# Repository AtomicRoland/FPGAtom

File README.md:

# FPGAtom

These are the KiCad files of the MK2 boards for the Atom 2k18 a.k.a. FPGAtom. The production files of the MK1 boards are also included but you don't want to use these :-).

For support, create an issue on Github or post your question or remark on the StarDot forums: https://stardot.org.uk/forums/viewtopic.php?f=44&t=15197

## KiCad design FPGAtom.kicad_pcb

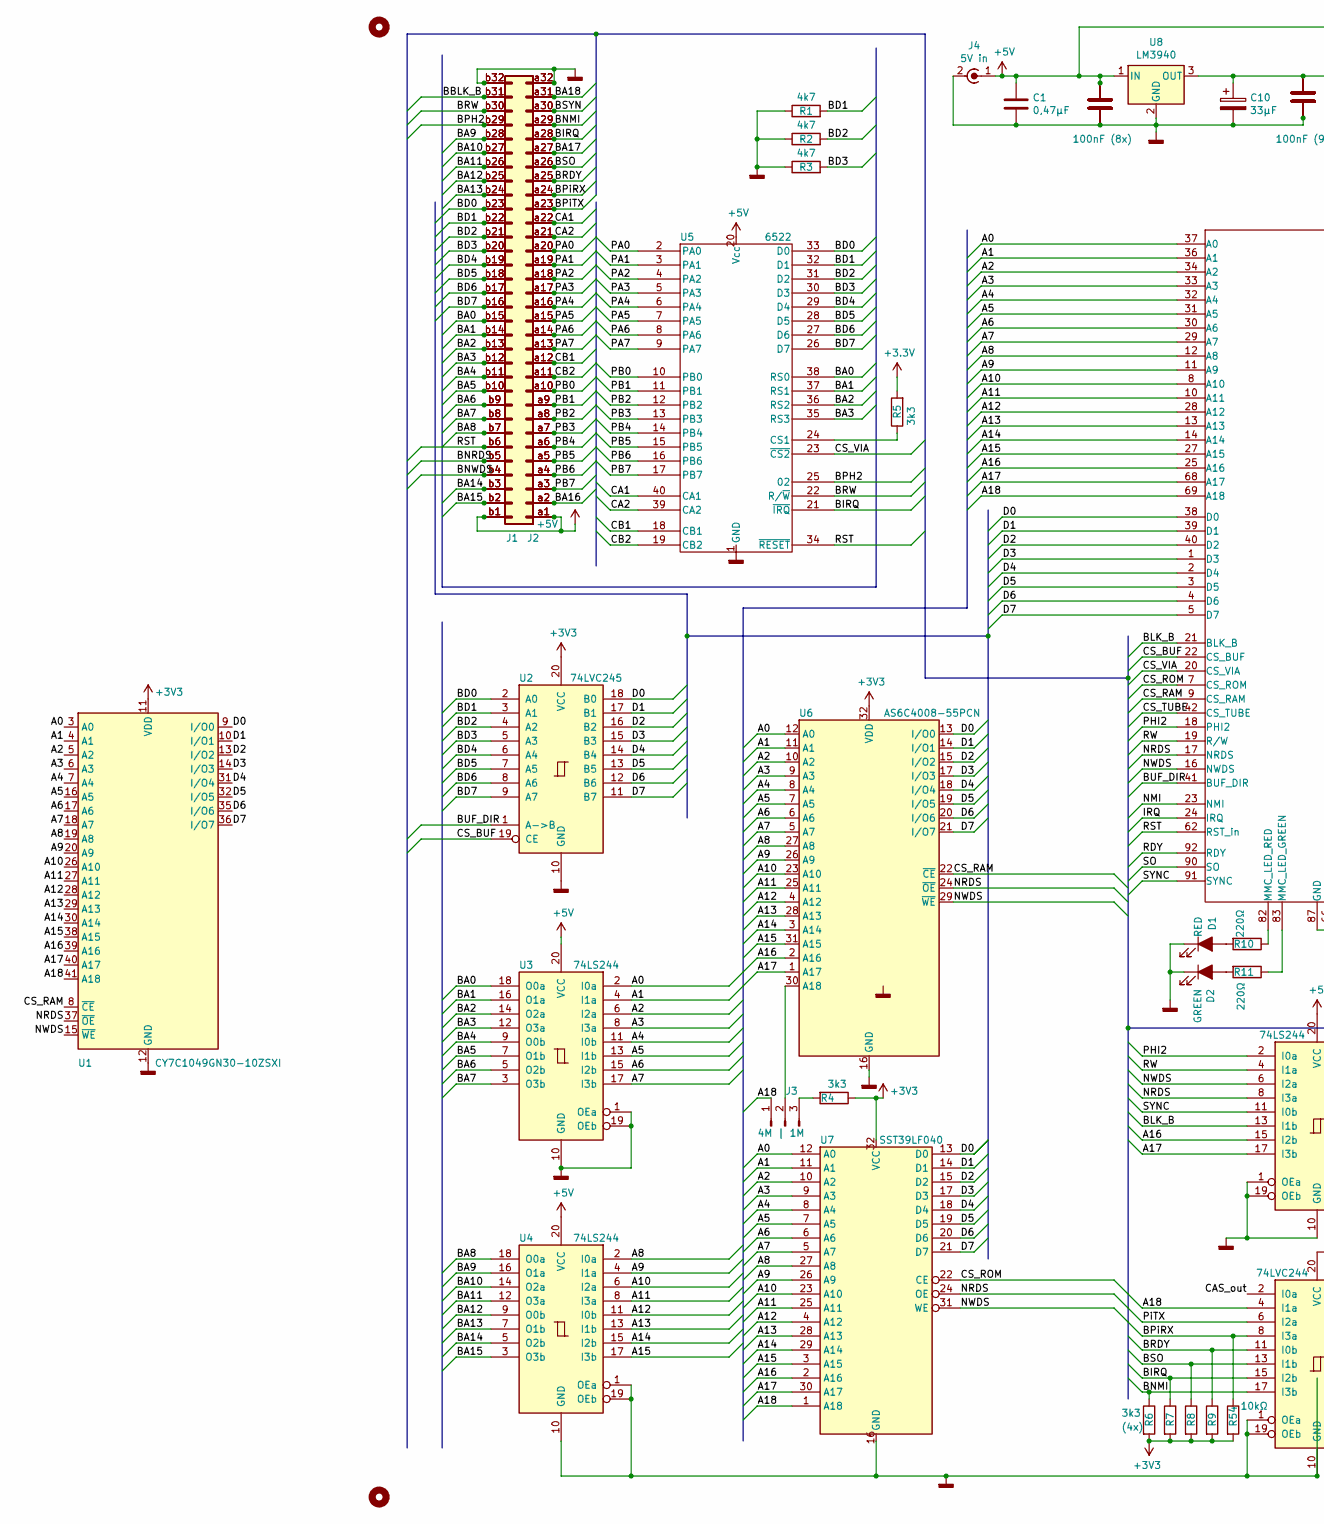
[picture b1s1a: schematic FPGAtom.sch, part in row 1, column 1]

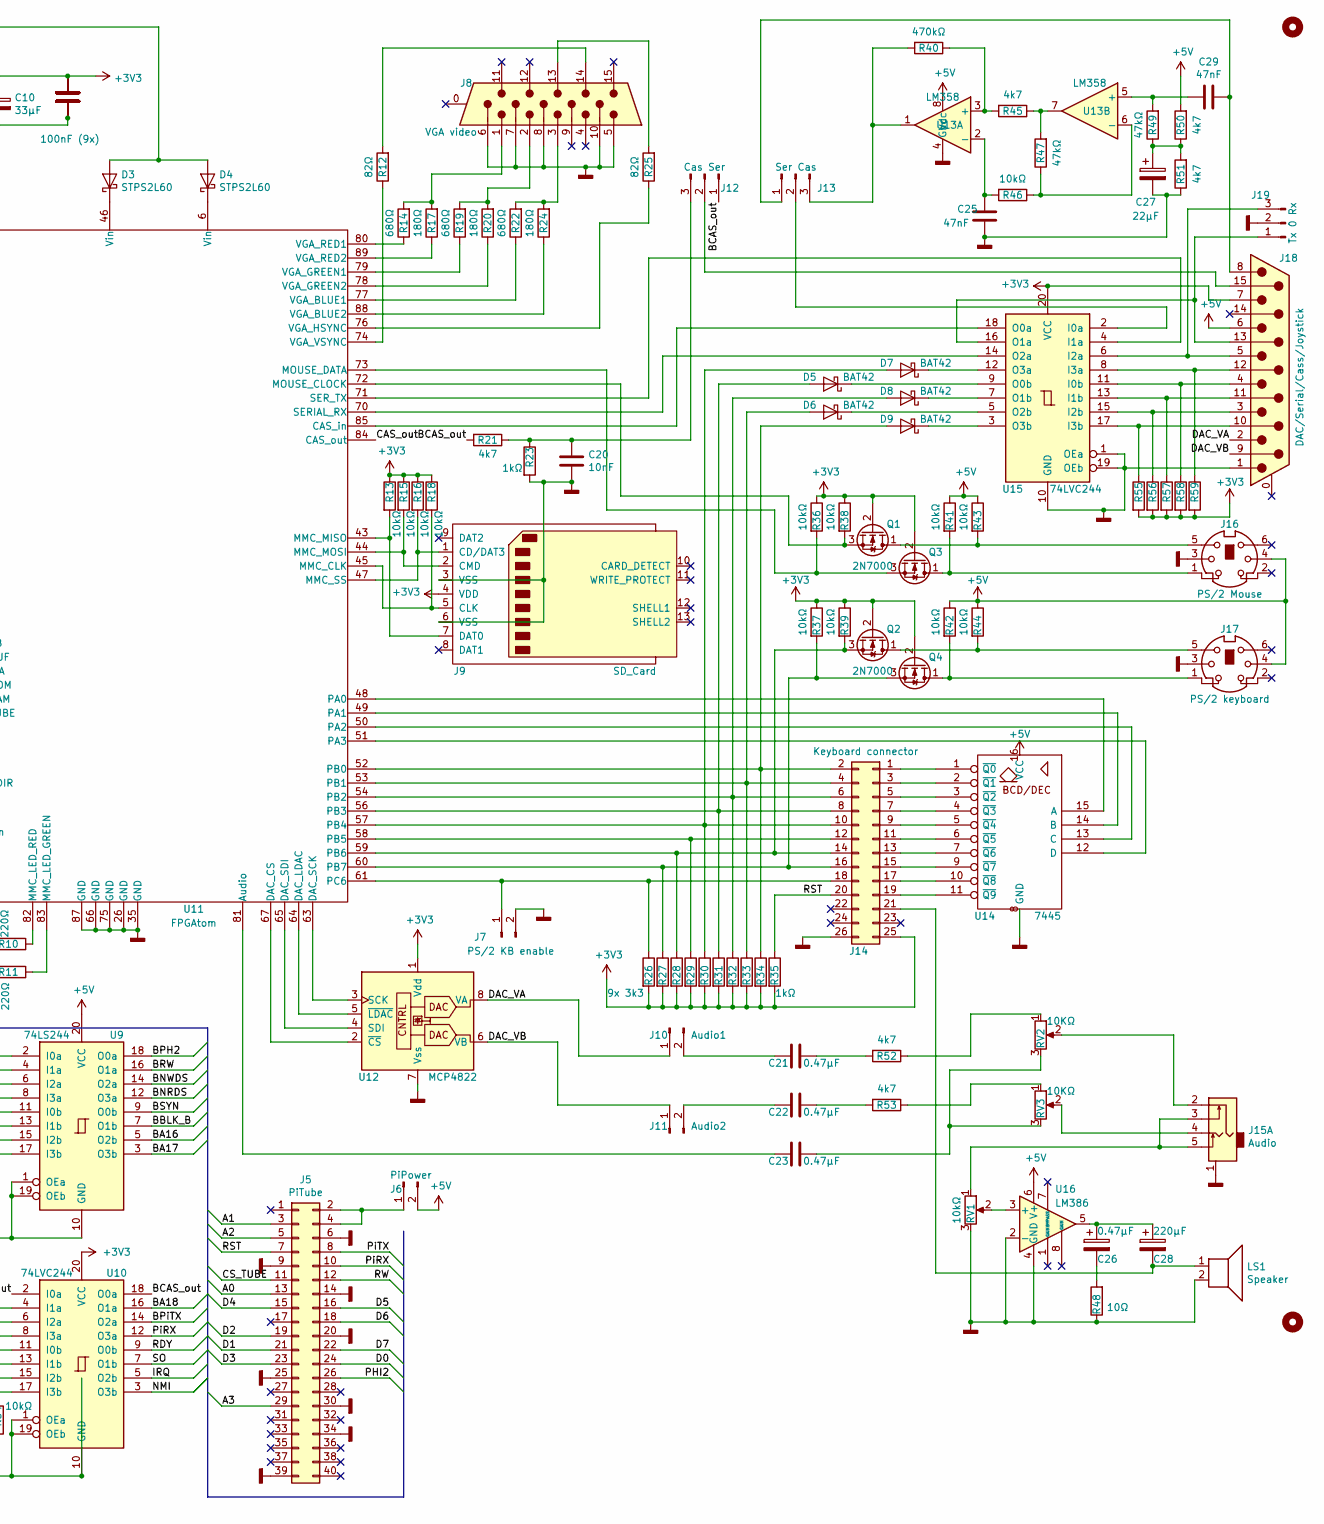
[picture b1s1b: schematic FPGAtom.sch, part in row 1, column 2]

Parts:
C1: 0,47µF; CP_Radial_D10.0mm_P5.00mm
C2, C3, C4, C5, C6, C7, C9, C11, C12, C13, C14, C15, C16, C17, C18: 100nF; C_Rect_L10.0mm_W4.0mm_P7.50mm_MKS4
C8: 100nF (8x); C_Rect_L10.0mm_W4.0mm_P7.50mm_MKS4
C10: 33µF; CP_Radial_D10.0mm_P5.00mm
C19: 100nF (9x); C_Rect_L10.0mm_W4.0mm_P7.50mm_MKS4
C20: 10nF; C_Rect_L10.0mm_W4.0mm_P7.50mm_MKS4
C21, C22, C23: 0.47µF; C_Rect_L10.0mm_W4.0mm_P7.50mm_MKS4
C25, C29: 47nF; C_Rect_L10.0mm_W4.0mm_P7.50mm_MKS4
C26: 0.47µF; CP_Radial_D10.0mm_P5.00mm
C27: 22µF; CP_Radial_D10.0mm_P5.00mm
C28: 220µF; CP_Radial_D10.0mm_P5.00mm
D1: RED; LED_D3.0mm
D2: GREEN; LED_D3.0mm
D3, D4: STPS2L60; D_DO-41_SOD81_P10.16mm_Horizontal
D5, D6, D7, D8, D9: BAT42; D_A-405_P7.62mm_Horizontal
H1, H2: MountingHole; MountingHole_4mm
H3, H4: MountingHole; MountingHole_6mm
J1: Conn_02x32_Row_Letter_First; DIN41612_B_2x32_Vertical
J2: Conn_02x32_Row_Letter_First; DIN41612_B_2x32_Horizontal
J3: 4M | 1M; Socket_Strip_Straight_1x03_Pitch2.54mm
J4: 5V in; BARREL_JACK
J5: PiTube; Socket_Strip_Straight_2x20_Pitch2.54mm
J6: PiPower; Socket_Strip_Straight_1x02_Pitch2.54mm
J7: PS/2 KB enable; Socket_Strip_Straight_1x02_Pitch2.54mm
J8: VGA video; DSUB-15-HD_Male_Horizontal_P2.29x1.98mm_EdgePinOffset8.35mm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
J9: SD_Card; SD-MMC
J10: Audio1; Socket_Strip_Straight_1x02_Pitch2.54mm
J11: Audio2; Socket_Strip_Straight_1x02_Pitch2.54mm
J12: Cas Ser; Socket_Strip_Straight_1x03_Pitch2.54mm
J13: Ser Cas; Socket_Strip_Straight_1x03_Pitch2.54mm
J14: Keyboard connector; Pin_Header_Straight_2x13_Pitch2.54mm
J15: Audio; Jack_35_5p
J16: PS/2 Mouse; PS2
J17: PS/2 keyboard; PS2
J18: DAC/Serial/Cass/Joystick; DSUB-15_Female_Horizontal_P2.77x2.84mm_EdgePinOffset4.94mm_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
J19: Tx 0 Rx; Socket_Strip_Straight_1x03_Pitch2.54mm
LS1: Speaker; Socket_Strip_Straight_1x02_Pitch2.54mm
Q1, Q2: 2N7000; TO-92_Inline_Wide
Q3, Q4: BS170; TO-92_Inline_Wide
R1, R2, R3, R21, R45, R50, R51, R52, R53: 4k7; R_Axial_DIN0207_L6.3mm_D2.5mm_P7.62mm_Horizontal
R4, R5, R9, R55, R56, R57, R58, R59: 3k3; R_Axial_DIN0207_L6.3mm_D2.5mm_P7.62mm_Horizontal
R6, R7, R27, R28, R29, R30, R31, R32, R33, R34: R; R_Axial_DIN0207_L6.3mm_D2.5mm_P7.62mm_Horizontal
R8: (4x); R_Axial_DIN0207_L6.3mm_D2.5mm_P7.62mm_Horizontal
R10, R11: 220Ω; R_Axial_DIN0207_L6.3mm_D2.5mm_P7.62mm_Horizontal
R12, R25: 82Ω; R_Axial_DIN0207_L6.3mm_D2.5mm_P7.62mm_Horizontal
R13, R15, R16, R18, R36, R37, R38, R39, R41, R42, R43, R44, R46, R54: 10kΩ; R_Axial_DIN0207_L6.3mm_D2.5mm_P7.62mm_Horizontal
R14, R19, R22: 680Ω; R_Axial_DIN0207_L6.3mm_D2.5mm_P7.62mm_Horizontal
R17, R20, R24: 180Ω; R_Axial_DIN0207_L6.3mm_D2.5mm_P7.62mm_Horizontal
R23, R35: 1kΩ; R_Axial_DIN0207_L6.3mm_D2.5mm_P7.62mm_Horizontal
R26: 9x 3k3; R_Axial_DIN0207_L6.3mm_D2.5mm_P7.62mm_Horizontal
R40: 470kΩ; R_Axial_DIN0207_L6.3mm_D2.5mm_P7.62mm_Horizontal
R47, R49: 47kΩ; R_Axial_DIN0207_L6.3mm_D2.5mm_P7.62mm_Horizontal
R48: 10Ω; R_Axial_DIN0207_L6.3mm_D2.5mm_P7.62mm_Horizontal
RV1: 10kΩ; Potentiometer_Trimmer_Suntan_TSR-3386P_Horizontal
RV2, RV3: 10KΩ; Potentiometer_Trimmer_Suntan_TSR-3386P_Horizontal
U1: CY7C1049GN30-10ZSXI; TSOP-II-44_10.16x18.41mm_P0.8mm
U2: 74LVC245; DIP-20_W7.62mm_Socket
U3, U4, U9: 74LS244; DIP-20_W7.62mm_Socket
U5: 6522; DIP-40_W15.24mm_Socket
U6: AS6C4008-55PCN; DIP-32_W15.24mm_Socket
U7: SST39LF040; PLCC-32_THT-Socket
U8: LM3940; TO-220-3_Horizontal
U10, U15: 74LVC244; DIP-20_W7.62mm_Socket
U11: FPGAtom; FPGAmodule
U12: MCP4822; DIP-8_W7.62mm_Socket
U13: LM358; DIP-8_W7.62mm_Socket
U14: 7445; DIP-16_W7.62mm_Socket
U16: LM386; DIP-8_W7.62mm_Socket

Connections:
+5V: C1.1, C2.1, C3.1, C4.1, C5.1, C6.1, C7.1, C8.1, C9.1, D3.2 (A), D4.2 (A), J1.a1, J1.b1, J2.a1, J2.b1, J4.1 (In), J6.2, J16.4, J17.4, J18.6, R41.1, R42.1, R43.1, R44.1, R50.2, U3.20 (VCC), U4.20 (VCC), U5.20 (Vcc), U8.1 (IN), U9.20 (VCC), U13.8 (Vcc), U14.16 (VCC), U16.6 (V+); also elsewhere on the board
/A0: J5.13, U1.3 (A0), U3.2 (I0a), U6.12 (A0), U7.12 (A0), U11.37 (A0); also elsewhere on the board
/A1: J5.3, U1.4 (A1), U3.4 (I1a), U6.11 (A1), U7.11 (A1), U11.36 (A1); also elsewhere on the board
/A2: J5.5, U1.5 (A2), U3.6 (I2a), U6.10 (A2), U7.10 (A2), U11.34 (A2); also elsewhere on the board
/A3: J5.29, U1.6 (A3), U3.8 (I3a), U6.9 (A3), U7.9 (A3), U11.33 (A3); also elsewhere on the board
/A4: U1.7 (A4), U3.11 (I0b), U6.8 (A4), U7.8 (A4), U11.32 (A4)
/A5: U1.16 (A5), U3.13 (I1b), U6.7 (A5), U7.7 (A5), U11.31 (A5)
/A6: U1.17 (A6), U3.15 (I2b), U6.6 (A6), U7.6 (A6), U11.30 (A6)
/A7: U1.18 (A7), U3.17 (I3b), U6.5 (A7), U7.5 (A7), U11.29 (A7)
/A8: U1.19 (A8), U4.2 (I0a), U6.27 (A8), U7.27 (A8), U11.12 (A8)
/A9: U1.20 (A9), U4.4 (I1a), U6.26 (A9), U7.26 (A9), U11.11 (A9)
/A10: U1.26 (A10), U4.6 (I2a), U6.23 (A10), U7.23 (A10), U11.8 (A10)
/A11: U1.27 (A11), U4.8 (I3a), U6.25 (A11), U7.25 (A11), U11.10 (A11)
/A12: U1.28 (A12), U4.11 (I0b), U6.4 (A12), U7.4 (A12), U11.28 (A12)
/A13: U1.29 (A13), U4.13 (I1b), U6.28 (A13), U7.28 (A13), U11.13 (A13)
/A14: U1.30 (A14), U4.15 (I2b), U6.3 (A14), U7.29 (A14), U11.14 (A14)
/A15: U1.38 (A15), U4.17 (I3b), U6.31 (A15), U7.3 (A15), U11.27 (A15)
/A16: U1.39 (A16), U6.2 (A16), U7.2 (A16), U9.15 (I2b), U11.25 (A16)
/A17: U1.40 (A17), U6.1 (A17), U7.30 (A17), U9.17 (I3b), U11.68 (A17)
/A18: J3.1, U1.41 (A18), U7.1 (A18), U10.4 (I1a), U11.69 (A18)
/BA0: J1.b15, J2.b15, U3.18 (O0a), U5.38 (RS0); also elsewhere on the board
/BA1: J1.b14, J2.b14, U3.16 (O1a), U5.37 (RS1); also elsewhere on the board
/BA2: J1.b13, J2.b13, U3.14 (O2a), U5.36 (RS2); also elsewhere on the board
/BA3: J1.b12, J2.b12, U3.12 (O3a), U5.35 (RS3); also elsewhere on the board
/BA4: J1.b11, J2.b11, U3.9 (O0b); also elsewhere on the board
/BA5: J1.b10, J2.b10, U3.7 (O1b); also elsewhere on the board
/BA6: J1.b9, J2.b9, U3.5 (O2b); also elsewhere on the board
/BA7: J1.b8, J2.b8, U3.3 (O3b); also elsewhere on the board
/BA8: J1.b7, J2.b7, U4.18 (O0a); also elsewhere on the board
/BA9: J1.b28, J2.b28, U4.16 (O1a); also elsewhere on the board
/BA10: J1.b27, J2.b27, U4.14 (O2a); also elsewhere on the board
/BA11: J1.b26, J2.b26, U4.12 (O3a); also elsewhere on the board
/BA12: J1.b25, J2.b25, U4.9 (O0b); also elsewhere on the board
/BA13: J1.b24, J2.b24, U4.7 (O1b); also elsewhere on the board
/BA14: J1.b3, J2.b3, U4.5 (O2b); also elsewhere on the board
/BA15: J1.b2, J2.b2, U4.3 (O3b); also elsewhere on the board
/BA16: J1.a2, J2.a2, U9.5 (O2b); also elsewhere on the board
/BA17: J1.a27, J2.a27, U9.3 (O3b); also elsewhere on the board
/BA18: J1.a31, J2.a31, U10.16 (O1a); also elsewhere on the board
/BBLK_B: J1.b31, J2.b31, U9.7 (O1b); also elsewhere on the board
/BCAS_out: J12.1, R21.2, U10.18 (O0a)
/BD0: J1.b23, J2.b23, U2.2 (A0), U5.33 (D0); also elsewhere on the board
/BD1: J1.b22, J2.b22, R1.2, U2.3 (A1), U5.32 (D1); also elsewhere on the board
/BD2: J1.b21, J2.b21, R2.2, U2.4 (A2), U5.31 (D2); also elsewhere on the board
/BD3: J1.b20, J2.b20, R3.2, U2.5 (A3), U5.30 (D3); also elsewhere on the board
/BD4: J1.b19, J2.b19, U2.6 (A4), U5.29 (D4); also elsewhere on the board
/BD5: J1.b18, J2.b18, U2.7 (A5), U5.28 (D5); also elsewhere on the board
/BD6: J1.b17, J2.b17, U2.8 (A6), U5.27 (D6); also elsewhere on the board
/BD7: J1.b16, J2.b16, U2.9 (A7), U5.26 (D7); also elsewhere on the board
/BIRQ: J1.a28, J2.a28, R7.1, U5.21 (~IRQ), U10.15 (I2b); also elsewhere on the board
/BLK_B: U9.13 (I1b), U11.21 (BLK_B)
/BNMI: J1.a29, J2.a29, R6.1, U10.17 (I3b); also elsewhere on the board
/BNRDS: J1.b5, J2.b5, U9.12 (O3a); also elsewhere on the board
/BNWDS: J1.b4, J2.b4, U9.14 (O2a); also elsewhere on the board
/BPH2: J1.b29, J2.b29, U5.25 (02), U9.18 (O0a); also elsewhere on the board
/BPiRX: J1.a24, J2.a24, R54.1, U10.8 (I3a); also elsewhere on the board
/BPiTX: J1.a23, J2.a23, U10.14 (O2a); also elsewhere on the board
/BRDY: J1.a25, J2.a25, R9.1, U10.11 (I0b); also elsewhere on the board
/BRW: J1.b30, J2.b30, U5.22 (R/~W), U9.16 (O1a); also elsewhere on the board
/BSO: J1.a26, J2.a26, R8.1, U10.13 (I1b); also elsewhere on the board
/BSYN: J1.a30, J2.a30, U9.9 (O0b); also elsewhere on the board
/BUF_DIR: U2.1 (A->B), U11.41 (BUF_DIR)
/CA1: J1.a22, J2.a22, U5.40 (CA1); also elsewhere on the board
/CA2: J1.a21, J2.a21, U5.39 (CA2); also elsewhere on the board
/CAS_out: U10.2 (I0a), U11.84 (CAS_out)
/CB1: J1.a12, J2.a12, U5.18 (CB1); also elsewhere on the board
/CB2: J1.a11, J2.a11, U5.19 (CB2); also elsewhere on the board
/CS_BUF: U2.19 (CE), U11.22 (CS_BUF)
/CS_RAM: U1.8 (~CE), U6.22 (~CE), U11.9 (CS_RAM)
/CS_ROM: U7.22 (CE), U11.7 (CS_ROM)
/CS_TUBE: J5.11, U11.42 (CS_TUBE); also elsewhere on the board
/CS_VIA: U5.23 (~CS2), U11.20 (CS_VIA)
/D0: J5.24, U1.9 (I/O0), U2.18 (B0), U6.13 (I/O0), U7.13 (D0), U11.38 (D0); also elsewhere on the board
/D1: J5.21, U1.10 (I/O1), U2.17 (B1), U6.14 (I/O1), U7.14 (D1), U11.39 (D1); also elsewhere on the board
/D2: J5.19, U1.13 (I/O2), U2.16 (B2), U6.15 (I/O2), U7.15 (D2), U11.40 (D2); also elsewhere on the board
/D3: J5.23, U1.14 (I/O3), U2.15 (B3), U6.17 (I/O3), U7.17 (D3), U11.1 (D3); also elsewhere on the board
/D4: J5.15, U1.31 (I/O4), U2.14 (B4), U6.18 (I/O4), U7.18 (D4), U11.2 (D4); also elsewhere on the board
/D5: J5.16, U1.32 (I/O5), U2.13 (B5), U6.19 (I/O5), U7.19 (D5), U11.3 (D5); also elsewhere on the board
/D6: J5.18, U1.35 (I/O6), U2.12 (B6), U6.20 (I/O6), U7.20 (D6), U11.4 (D6); also elsewhere on the board
/D7: J5.22, U1.36 (I/O7), U2.11 (B7), U6.21 (I/O7), U7.21 (D7), U11.5 (D7); also elsewhere on the board
/DAC_VA: J10.1, J18.2, U12.8 (VA)
/DAC_VB: J11.1, J18.9, U12.6 (VB)
/IRQ: U10.5 (O2b), U11.24 (IRQ)
/NMI: U10.3 (O3b), U11.23 (NMI)
/NRDS: U1.37 (~OE), U6.24 (~OE), U7.24 (OE), U9.8 (I3a), U11.17 (NRDS)
/NWDS: U1.15 (~WE), U6.29 (~WE), U7.31 (WE), U9.6 (I2a), U11.16 (NWDS)
/PA0: J1.a20, J2.a20, U5.2 (PA0); also elsewhere on the board
/PA1: J1.a19, J2.a19, U5.3 (PA1); also elsewhere on the board
/PA2: J1.a18, J2.a18, U5.4 (PA2); also elsewhere on the board
/PA3: J1.a17, J2.a17, U5.5 (PA3); also elsewhere on the board
/PA4: J1.a16, J2.a16, U5.6 (PA4); also elsewhere on the board
/PA5: J1.a15, J2.a15, U5.7 (PA5); also elsewhere on the board
/PA6: J1.a14, J2.a14, U5.8 (PA6); also elsewhere on the board
/PA7: J1.a13, J2.a13, U5.9 (PA7); also elsewhere on the board
/PB0: J1.a10, J2.a10, U5.10 (PB0); also elsewhere on the board
/PB1: J1.a9, J2.a9, U5.11 (PB1); also elsewhere on the board
/PB2: J1.a8, J2.a8, U5.12 (PB2); also elsewhere on the board
/PB3: J1.a7, J2.a7, U5.13 (PB3); also elsewhere on the board
/PB4: J1.a6, J2.a6, U5.14 (PB4); also elsewhere on the board
/PB5: J1.a5, J2.a5, U5.15 (PB5); also elsewhere on the board
/PB6: J1.a4, J2.a4, U5.16 (PB6); also elsewhere on the board
/PB7: J1.a3, J2.a3, U5.17 (PB7); also elsewhere on the board
/PHI2: J5.26, U9.2 (I0a), U11.18 (PHI2); also elsewhere on the board
/PiRX: J5.10, U10.12 (O3a); also elsewhere on the board
/PiTX: J5.8, U10.6 (I2a); also elsewhere on the board
/RDY: U10.9 (O0b), U11.92 (RDY)
/RST: J1.b6, J2.b6, J5.7, J14.20, R35.1, U5.34 (~RESET), U11.62 (RST_in); also elsewhere on the board
/RW: J5.12, U9.4 (I1a), U11.19 (R/W); also elsewhere on the board
/SO: U10.7 (O1b), U11.90 (SO)
/SYNC: U9.11 (I0b), U11.91 (SYNC)
GNDD: C1.2, C2.2, C3.2, C4.2, C5.2, C6.2, C7.2, C8.2, C9.2, C10.2, C11.2, C12.2, C13.2, C14.2, C15.2, C16.2, C17.2, C18.2, C19.2, C20.2, C25.2, C27.2, D1.1 (K), D2.1 (K), J1.a32, J1.b32, J2.a32, J2.b32, J4.2 (Ext), J5.6, J5.9, J5.14, J5.20, J5.25, J5.30, J5.34, J5.39, J7.2, J8.5, J8.6, J8.7, J8.8, J8.10, J9.3 (VSS), J9.6 (VSS), J14.26, J15.1, J16.3, J17.3, J18.1, J19.2, LS1.2, R1.1, R2.1, R3.1, R23.2, R48.1, R51.1, RV1.3, U1.12 (GND), U1.34 (GND), U2.10 (GND), U3.1 (OEa), U3.10 (GND), U3.19 (OEb), U4.1 (OEa), U4.10 (GND), U4.19 (OEb), U5.1 (GND), U6.16 (GND), U7.16 (GND), U8.2 (GND), U9.1 (OEa), U9.10 (GND), U9.19 (OEb), U10.1 (OEa), U10.10 (GND), U10.19 (OEb), U11.26 (GND), U11.35 (GND), U11.66 (GND), U11.75 (GND), U11.87 (GND), U12.7 (Vss), U13.4 (Gnd), U14.8 (GND), U15.1 (OEa), U15.10 (GND), U15.19 (OEb), U16.2 (-), U16.4 (GND); also elsewhere on the board
unnamed: C20.1, J12.3, R21.1, R23.1
unnamed: C21.1, R52.2
unnamed: C21.2, J10.2
unnamed: C22.1, R53.2
unnamed: C22.2, J11.2
unnamed: C23.1, RV2.3, RV3.3
unnamed: C23.2, U11.81 (Audio)
unnamed: C25.1, R46.2, U13.2 (-)
unnamed: C26.1, C28.1, U16.5
unnamed: C26.2, R48.2
unnamed: C27.1, R49.1, R50.1, R51.2
unnamed 122: C28.2, J14.21, LS1.1; also elsewhere on the board
unnamed: C29.1, J13.1, J18.8
unnamed: C29.2, R49.2, U13.5 (+)
unnamed: D1.2 (A), R10.2
unnamed: D2.2 (A), R11.2
unnamed: D3.1 (K), U11.46 (Vin)
unnamed: D4.1 (K), U11.6 (Vin)
unnamed: D5.1 (K), U15.9 (O0b)
unnamed: D5.2 (A), J14.8, R31.1, U11.56 (PB3)
unnamed: D6.1 (K), U15.5 (O2b)
unnamed: D6.2 (A), J14.4, R33.1, U11.53 (PB1)
unnamed: D7.1 (K), U15.12 (O3a)
unnamed: D7.2 (A), J14.10, R30.1, U11.57 (PB4)
unnamed: D8.1 (K), U15.7 (O1b)
unnamed: D8.2 (A), J14.6, R32.1, U11.54 (PB2)
unnamed: D9.1 (K), U15.3 (O3b)
unnamed: D9.2 (A), J14.2, R34.1, U11.52 (PB0)
unnamed: J3.2, U6.30 (A18)
unnamed: J3.3, R4.2
unnamed 141: J5.2, J5.4, J6.1; also elsewhere on the board
unnamed: J8.1, R14.2, R17.2
unnamed: J8.2, R19.2, R20.2
unnamed: J8.3, R22.2, R24.2
unnamed: J8.13, R25.2
unnamed: J8.14, R12.2
unnamed: J9.1 (CD/DAT3), R16.2, U11.47 (MMC_SS)
unnamed: J9.2 (CMD), R15.2, U11.44 (MMC_MOSI)
unnamed: J9.5 (CLK), R18.2, U11.45 (MMC_CLK)
unnamed: J9.7 (DAT0), R13.2, U11.43 (MMC_MISO)
unnamed: J12.2, J18.15
unnamed: J13.2, U15.2 (I0a)
unnamed: J13.3, R40.2, U13.1
unnamed: J14.1, U14.1 (~Q0)
unnamed: J14.3, U14.2 (~Q1)
unnamed: J14.5, U14.3 (~Q2)
unnamed: J14.7, U14.4 (~Q3)
unnamed: J14.9, U14.5 (~Q4)
unnamed: J14.11, U14.6 (~Q5)
unnamed: J14.12, R29.1, U11.58 (PB5)
unnamed: J14.13, U14.7 (~Q6)
unnamed: J14.14, Q2.3 (S), R28.1, R39.2, U11.59 (PB6)
unnamed: J14.15, U14.9 (~Q7)
unnamed: J14.16, Q4.3 (S), R27.1, R37.2, U11.60 (PB7)
unnamed: J14.17, U14.10 (~Q8)
unnamed: J7.1, J14.18, R26.1, U11.61 (PC6)
unnamed: J14.19, U14.11 (~Q9)
unnamed: J15.2, RV2.2
unnamed: J15.3, J15.5, RV1.1
unnamed: J15.4, RV3.2
unnamed: J16.1, Q3.1 (D), R41.2
unnamed: J16.5, Q1.1 (D), R43.2
unnamed: J17.1, Q4.1 (D), R42.2
unnamed: J17.5, Q2.1 (D), R44.2
unnamed: J18.3, R56.1, U15.15 (I2b)
unnamed: J18.4, R58.1, U15.11 (I0b)
unnamed: J18.5, J19.3, U15.6 (I2a)
unnamed: J18.10, R55.1, U15.17 (I3b)
unnamed: J18.11 (P111), R57.1, U15.13 (I1b)
unnamed: J18.12, R59.1, U15.8 (I3a)
unnamed: J18.13, J19.1, U15.16 (O1a)
unnamed: Q1.3 (S), R38.2, U11.72 (MOUSE_CLOCK)
unnamed: Q3.3 (S), R36.2, U11.73 (MOUSE_DATA)
unnamed: R5.1, U5.24 (CS1)
unnamed: R10.1, U11.82 (MMC_LED_RED)
unnamed: R11.1, U11.83 (MMC_LED_GREEN)
unnamed: R12.1, U11.74 (VGA_VSYNC)
unnamed: R14.1, U11.80 (VGA_RED1)
unnamed: R17.1, U11.89 (VGA_RED2)
unnamed: R19.1, U11.79 (VGA_GREEN1)
unnamed: R20.1, U11.78 (VGA_GREEN2)
unnamed: R22.1, U11.77 (VGA_BLUE1)
unnamed: R24.1, U11.88 (VGA_BLUE2)
unnamed: R25.1, U11.76 (VGA_HSYNC)
unnamed: R40.1, R45.2, U13.3 (+)
unnamed: R45.1, R47.2, U13.7
unnamed: R46.1, R47.1, U13.6 (-)
unnamed: R52.1, RV2.1
unnamed: R53.1, RV3.1
unnamed: RV1.2, U16.3 (+)
unnamed: U11.48 (PA0), U14.15 (A)
unnamed: U11.49 (PA1), U14.14 (B)
unnamed: U11.50 (PA2), U14.13 (C)
unnamed: U11.51 (PA3), U14.12 (D)
unnamed: U11.63 (DAC_SCK), U12.3 (SCK)
unnamed: U11.64 (DAC_LDAC), U12.5 (~LDAC)
unnamed: U11.65 (DAC_SDI), U12.4 (SDI)
unnamed: U11.67 (DAC_CS), U12.2 (~CS)
unnamed: U11.70 (SERIAL_RX), U15.14 (O2a)
unnamed: U11.71 (SER_TX), U15.4 (I1a)
unnamed: U11.85 (CAS_in), U15.18 (O0a)

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
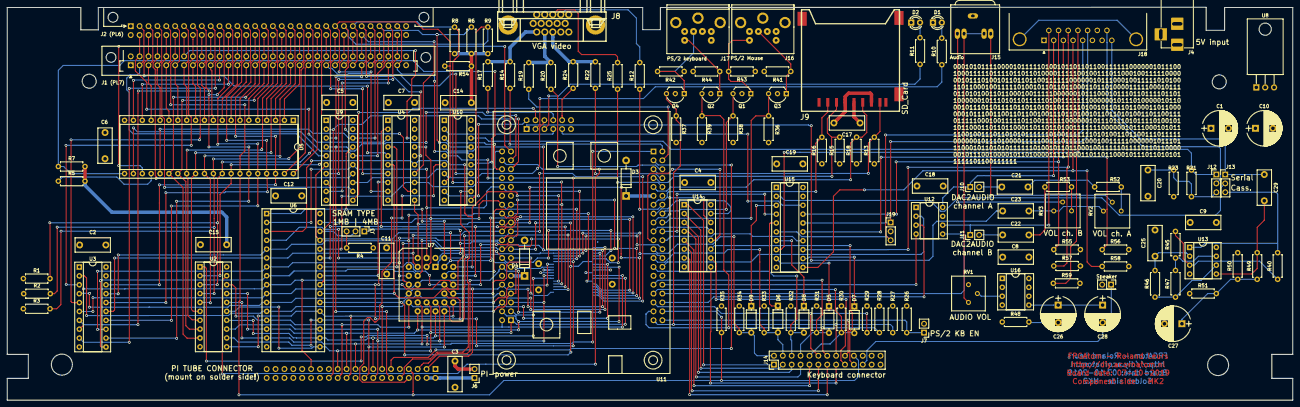
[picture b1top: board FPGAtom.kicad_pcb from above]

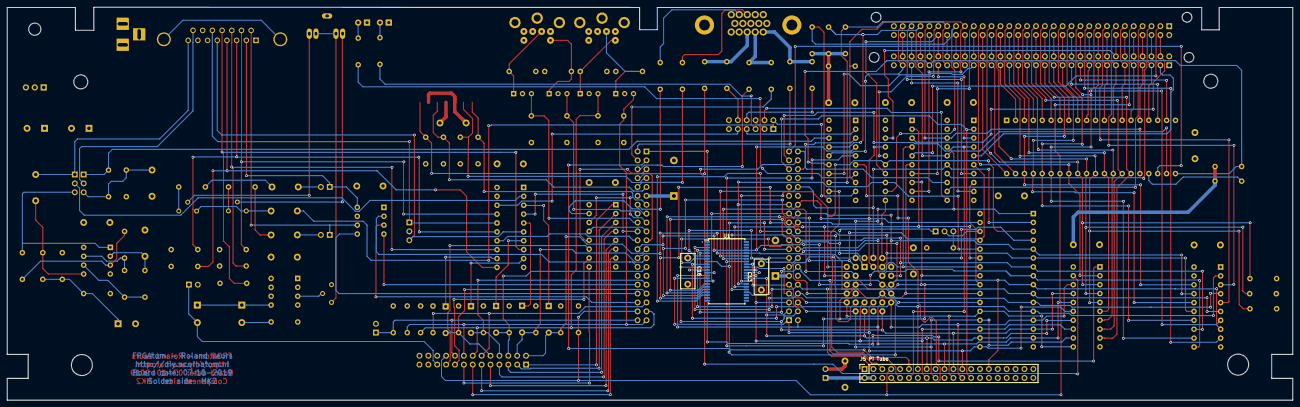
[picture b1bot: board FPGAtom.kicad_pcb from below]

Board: 4 copper layers, 367.5 x 112.3 mm, 143 parts (4 on the bottom side), 213 nets.

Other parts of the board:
J1 (PL7): Conn_02x32_Row_Letter_First; DIN41612_B_2x32_Vertical
J2 (PL6): Conn_02x32_Row_Letter_First; DIN41612_B_2x32_Horizontal
J5 Pi Tube: PiTube; Socket_Strip_Straight_2x20_Pitch2.54mm
Speaker: Speaker; Socket_Strip_Straight_2x01_Pitch2.54mm

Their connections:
+5V: J1 (PL7).a1, J1 (PL7).b1, J2 (PL6).a1, J2 (PL6).b1; also elsewhere on the board
/A0: J5 Pi Tube.13; also elsewhere on the board
/A1: J5 Pi Tube.3; also elsewhere on the board
/A2: J5 Pi Tube.5; also elsewhere on the board
/A3: J5 Pi Tube.29; also elsewhere on the board
/BA0: J1 (PL7).b15, J2 (PL6).b15; also elsewhere on the board
/BA1: J1 (PL7).b14, J2 (PL6).b14; also elsewhere on the board
/BA2: J1 (PL7).b13, J2 (PL6).b13; also elsewhere on the board
/BA3: J1 (PL7).b12, J2 (PL6).b12; also elsewhere on the board
/BA4: J1 (PL7).b11, J2 (PL6).b11; also elsewhere on the board
/BA5: J1 (PL7).b10, J2 (PL6).b10; also elsewhere on the board
/BA6: J1 (PL7).b9, J2 (PL6).b9; also elsewhere on the board
/BA7: J1 (PL7).b8, J2 (PL6).b8; also elsewhere on the board
/BA8: J1 (PL7).b7, J2 (PL6).b7; also elsewhere on the board
/BA9: J1 (PL7).b28, J2 (PL6).b28; also elsewhere on the board
/BA10: J1 (PL7).b27, J2 (PL6).b27; also elsewhere on the board
/BA11: J1 (PL7).b26, J2 (PL6).b26; also elsewhere on the board
/BA12: J1 (PL7).b25, J2 (PL6).b25; also elsewhere on the board
/BA13: J1 (PL7).b24, J2 (PL6).b24; also elsewhere on the board
/BA14: J1 (PL7).b3, J2 (PL6).b3; also elsewhere on the board
/BA15: J1 (PL7).b2, J2 (PL6).b2; also elsewhere on the board
/BA16: J1 (PL7).a2, J2 (PL6).a2; also elsewhere on the board
/BA17: J1 (PL7).a27, J2 (PL6).a27; also elsewhere on the board
/BA18: J1 (PL7).a31, J2 (PL6).a31; also elsewhere on the board
/BBLK_B: J1 (PL7).b31, J2 (PL6).b31; also elsewhere on the board
/BD0: J1 (PL7).b23, J2 (PL6).b23; also elsewhere on the board
/BD1: J1 (PL7).b22, J2 (PL6).b22; also elsewhere on the board
/BD2: J1 (PL7).b21, J2 (PL6).b21; also elsewhere on the board
/BD3: J1 (PL7).b20, J2 (PL6).b20; also elsewhere on the board
/BD4: J1 (PL7).b19, J2 (PL6).b19; also elsewhere on the board
/BD5: J1 (PL7).b18, J2 (PL6).b18; also elsewhere on the board
/BD6: J1 (PL7).b17, J2 (PL6).b17; also elsewhere on the board
/BD7: J1 (PL7).b16, J2 (PL6).b16; also elsewhere on the board
/BIRQ: J1 (PL7).a28, J2 (PL6).a28; also elsewhere on the board
/BNMI: J1 (PL7).a29, J2 (PL6).a29; also elsewhere on the board
/BNRDS: J1 (PL7).b5, J2 (PL6).b5; also elsewhere on the board
/BNWDS: J1 (PL7).b4, J2 (PL6).b4; also elsewhere on the board
/BPH2: J1 (PL7).b29, J2 (PL6).b29; also elsewhere on the board
/BPiRX: J1 (PL7).a24, J2 (PL6).a24; also elsewhere on the board
/BPiTX: J1 (PL7).a23, J2 (PL6).a23; also elsewhere on the board
/BRDY: J1 (PL7).a25, J2 (PL6).a25; also elsewhere on the board
/BRW: J1 (PL7).b30, J2 (PL6).b30; also elsewhere on the board
/BSO: J1 (PL7).a26, J2 (PL6).a26; also elsewhere on the board
/BSYN: J1 (PL7).a30, J2 (PL6).a30; also elsewhere on the board
/CA1: J1 (PL7).a22, J2 (PL6).a22; also elsewhere on the board
/CA2: J1 (PL7).a21, J2 (PL6).a21; also elsewhere on the board
/CB1: J1 (PL7).a12, J2 (PL6).a12; also elsewhere on the board
/CB2: J1 (PL7).a11, J2 (PL6).a11; also elsewhere on the board
/CS_TUBE: J5 Pi Tube.11; also elsewhere on the board
/D0: J5 Pi Tube.24; also elsewhere on the board
/D1: J5 Pi Tube.21; also elsewhere on the board
/D2: J5 Pi Tube.19; also elsewhere on the board
/D3: J5 Pi Tube.23; also elsewhere on the board
/D4: J5 Pi Tube.15; also elsewhere on the board
/D5: J5 Pi Tube.16; also elsewhere on the board
/D6: J5 Pi Tube.18; also elsewhere on the board
/D7: J5 Pi Tube.22; also elsewhere on the board
/PA0: J1 (PL7).a20, J2 (PL6).a20; also elsewhere on the board
/PA1: J1 (PL7).a19, J2 (PL6).a19; also elsewhere on the board
/PA2: J1 (PL7).a18, J2 (PL6).a18; also elsewhere on the board
/PA3: J1 (PL7).a17, J2 (PL6).a17; also elsewhere on the board
/PA4: J1 (PL7).a16, J2 (PL6).a16; also elsewhere on the board
/PA5: J1 (PL7).a15, J2 (PL6).a15; also elsewhere on the board
/PA6: J1 (PL7).a14, J2 (PL6).a14; also elsewhere on the board
/PA7: J1 (PL7).a13, J2 (PL6).a13; also elsewhere on the board
/PB0: J1 (PL7).a10, J2 (PL6).a10; also elsewhere on the board
/PB1: J1 (PL7).a9, J2 (PL6).a9; also elsewhere on the board
/PB2: J1 (PL7).a8, J2 (PL6).a8; also elsewhere on the board
/PB3: J1 (PL7).a7, J2 (PL6).a7; also elsewhere on the board
/PB4: J1 (PL7).a6, J2 (PL6).a6; also elsewhere on the board
/PB5: J1 (PL7).a5, J2 (PL6).a5; also elsewhere on the board
/PB6: J1 (PL7).a4, J2 (PL6).a4; also elsewhere on the board
/PB7: J1 (PL7).a3, J2 (PL6).a3; also elsewhere on the board
/PHI2: J5 Pi Tube.26; also elsewhere on the board
/PiRX: J5 Pi Tube.10; also elsewhere on the board
/PiTX: J5 Pi Tube.8; also elsewhere on the board
/RST: J1 (PL7).b6, J2 (PL6).b6, J5 Pi Tube.7; also elsewhere on the board
/RW: J5 Pi Tube.12; also elsewhere on the board
GNDD: J1 (PL7).a32, J1 (PL7).b32, J2 (PL6).a32, J2 (PL6).b32, J5 Pi Tube.6, J5 Pi Tube.9, J5 Pi Tube.14, J5 Pi Tube.20, J5 Pi Tube.25, J5 Pi Tube.30, J5 Pi Tube.34, Speaker.2; also elsewhere on the board
unnamed 122: Speaker.1; also elsewhere on the board
unnamed 141: J5 Pi Tube.2, J5 Pi Tube.4; also elsewhere on the board

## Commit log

2019-10-07 First commit of FPGAtom to Github.
